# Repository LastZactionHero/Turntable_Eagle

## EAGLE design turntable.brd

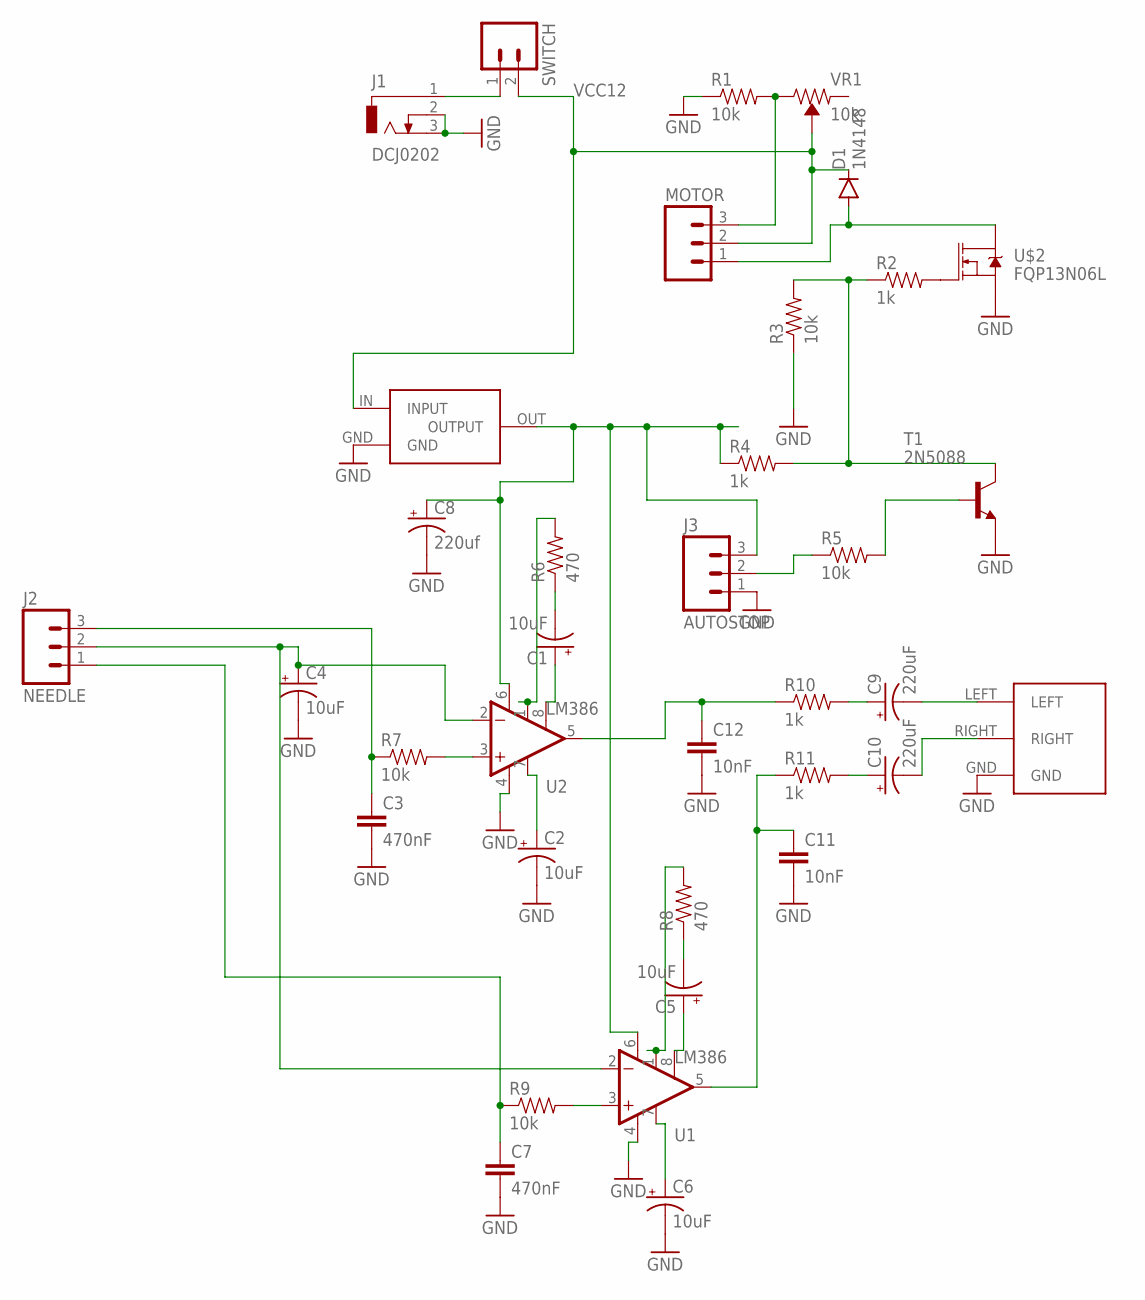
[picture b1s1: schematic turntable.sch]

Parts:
C1, C2, C4, C5, C6: 10uF; E5-5
C3, C7: 470nF; C15B8
C8: 220uf; TT5D10
C9, C10: 220uF; E5-5
C11, C12: 10nF; C5B2.5
D1: 1N4148; DIODE-1N4148
J1: DCJ0202
J2: NEEDLE; 1X03
J3: AUTOSTOP; 1X03
MOTOR: M03PTH; 1X03
R1, R3, R5, R7, R9: 10k; AXIAL-0.5
R2, R4, R10, R11: 1k; AXIAL-0.5
R6, R8: 470; AXIAL-0.5
SWITCH: M02PTH; 1X02
T1: 2N5088; TO92
U1, U2: LM386; DIP08
U$1: LD1117; 78XXL
U$2: FQP13N06L; TO-220
U$3: RCA
VR1: 10k; TRIMPOT-PTH-3386U

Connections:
GND: C2.-, C3.2, C4.-, C6.-, C7.2, C8.-, C11.2, C12.2, J1.2, J1.3, J3.1, R1.P$1 (1), R3.P$1 (1), T1.3 (E), U1.4 (V-), U2.4 (V-), U$1.GND, U$2.S, U$3.GND
unnamed: D1.A, MOTOR.1, U$2.D
unnamed: MOTOR.3, R1.P$2 (2), VR1.3 (CW)
unnamed: R2.P$2 (2), U$2.G
unnamed: R2.P$1 (1), R3.P$2 (2), R4.P$2 (2), T1.1 (C)
unnamed: C8.+, J3.3, R4.P$1 (1), U1.6 (V+), U2.6 (V+), U$1.OUT (OUTPUT)
unnamed: C1.-, R6.P$1 (1)
unnamed: J3.2, R5.P$1 (1)
unnamed: R5.P$2 (2), T1.2 (B)
unnamed: C1.+, U2.8 (GAIN)
unnamed: R6.P$2 (2), U2.1 (GAIN)
unnamed: C2.+, U2.7 (BP)
unnamed: C4.+, J2.2, U1.2 (-IN), U2.2 (-IN)
unnamed: C3.1, J2.3, R7.P$1 (1)
unnamed: R7.P$2 (2), U2.3 (+IN)
unnamed: C9.-, U$3.LEFT
unnamed: C9.+, R10.P$2 (2)
unnamed: C5.-, R8.P$1 (1)
unnamed: C5.+, U1.8 (GAIN)
unnamed: R8.P$2 (2), U1.1 (GAIN)
unnamed: C6.+, U1.7 (BP)
unnamed: C7.1, J2.1, R9.P$1 (1)
unnamed: R9.P$2 (2), U1.3 (+IN)
unnamed: C10.-, U$3.RIGHT
unnamed: C10.+, R11.P$2 (2)
unnamed: C12.1, R10.P$1 (1), U2.5 (OUT)
unnamed: C11.1, R11.P$1 (1), U1.5 (OUT)
unnamed: J1.1, SWITCH.1
VCC12: D1.C, MOTOR.2, SWITCH.2, U$1.IN (INPUT), VR1.2 (WIPER)

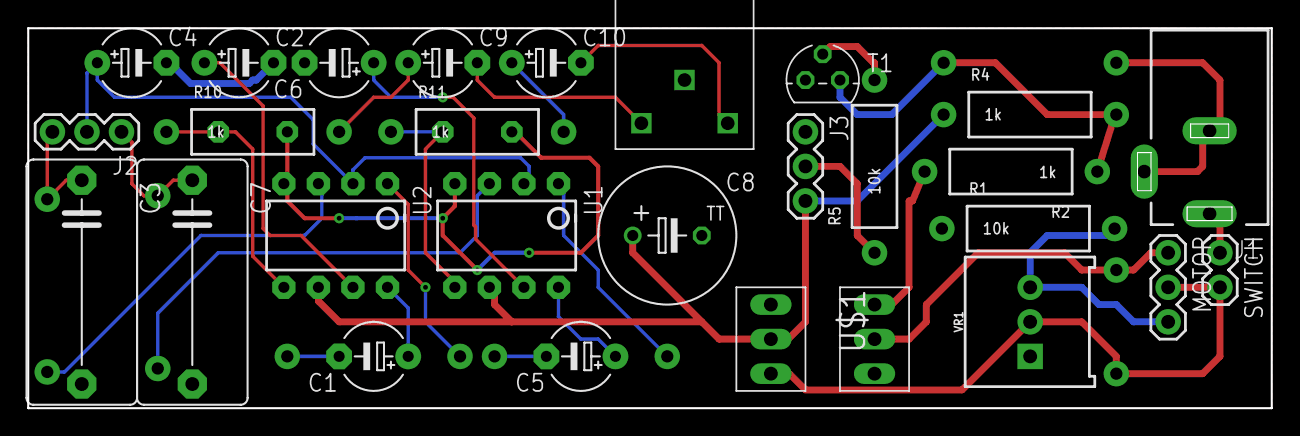
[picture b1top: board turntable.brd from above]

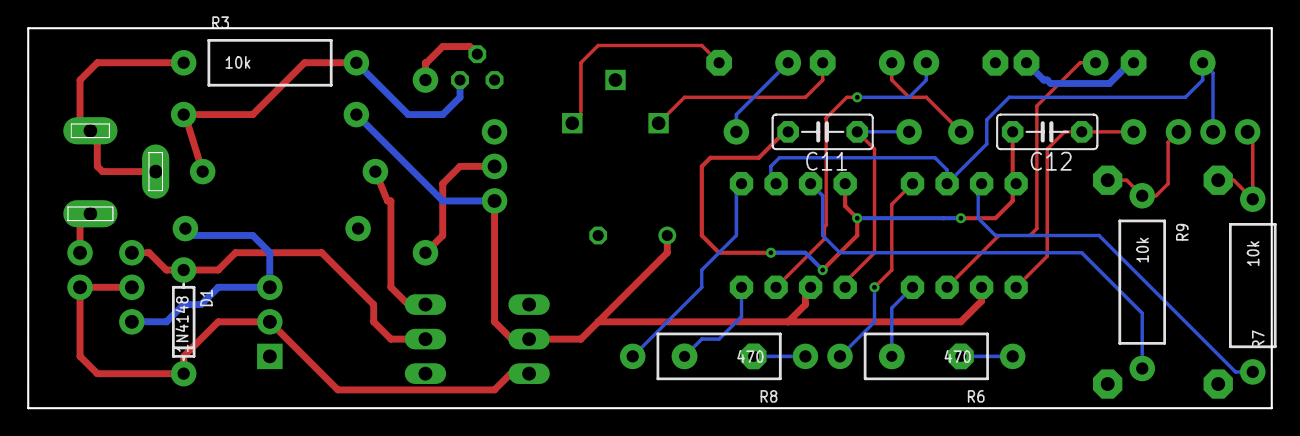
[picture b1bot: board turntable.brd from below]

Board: 2 copper layers, 91.4 x 27.9 mm, 36 parts (8 on the bottom side), 29 nets.

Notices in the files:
parts and their libraries:
SparkFun-AnalogIC: Licensing:Creative Commons ShareAlike 4.0 International - https://creativecommons.org/licenses/by-sa/4.0
